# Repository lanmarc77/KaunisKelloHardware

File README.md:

# KaunisKelloHardware
Hardware schematics of the Kaunis Kello clock

[firmware is here](https://github.com/lanmarc77/KaunisKello)

[firmware compiler](https://myiq.de/cgi-bin/kk.pl)

[hardware schematics are here](https://github.com/lanmarc77/KaunisKelloHardware)

[MP3 module code is here](https://github.com/lanmarc77/KaunisKelloSoundModule)

[SD card sounds of the MP3 module are here](https://github.com/lanmarc77/KaunisKelloSounds)

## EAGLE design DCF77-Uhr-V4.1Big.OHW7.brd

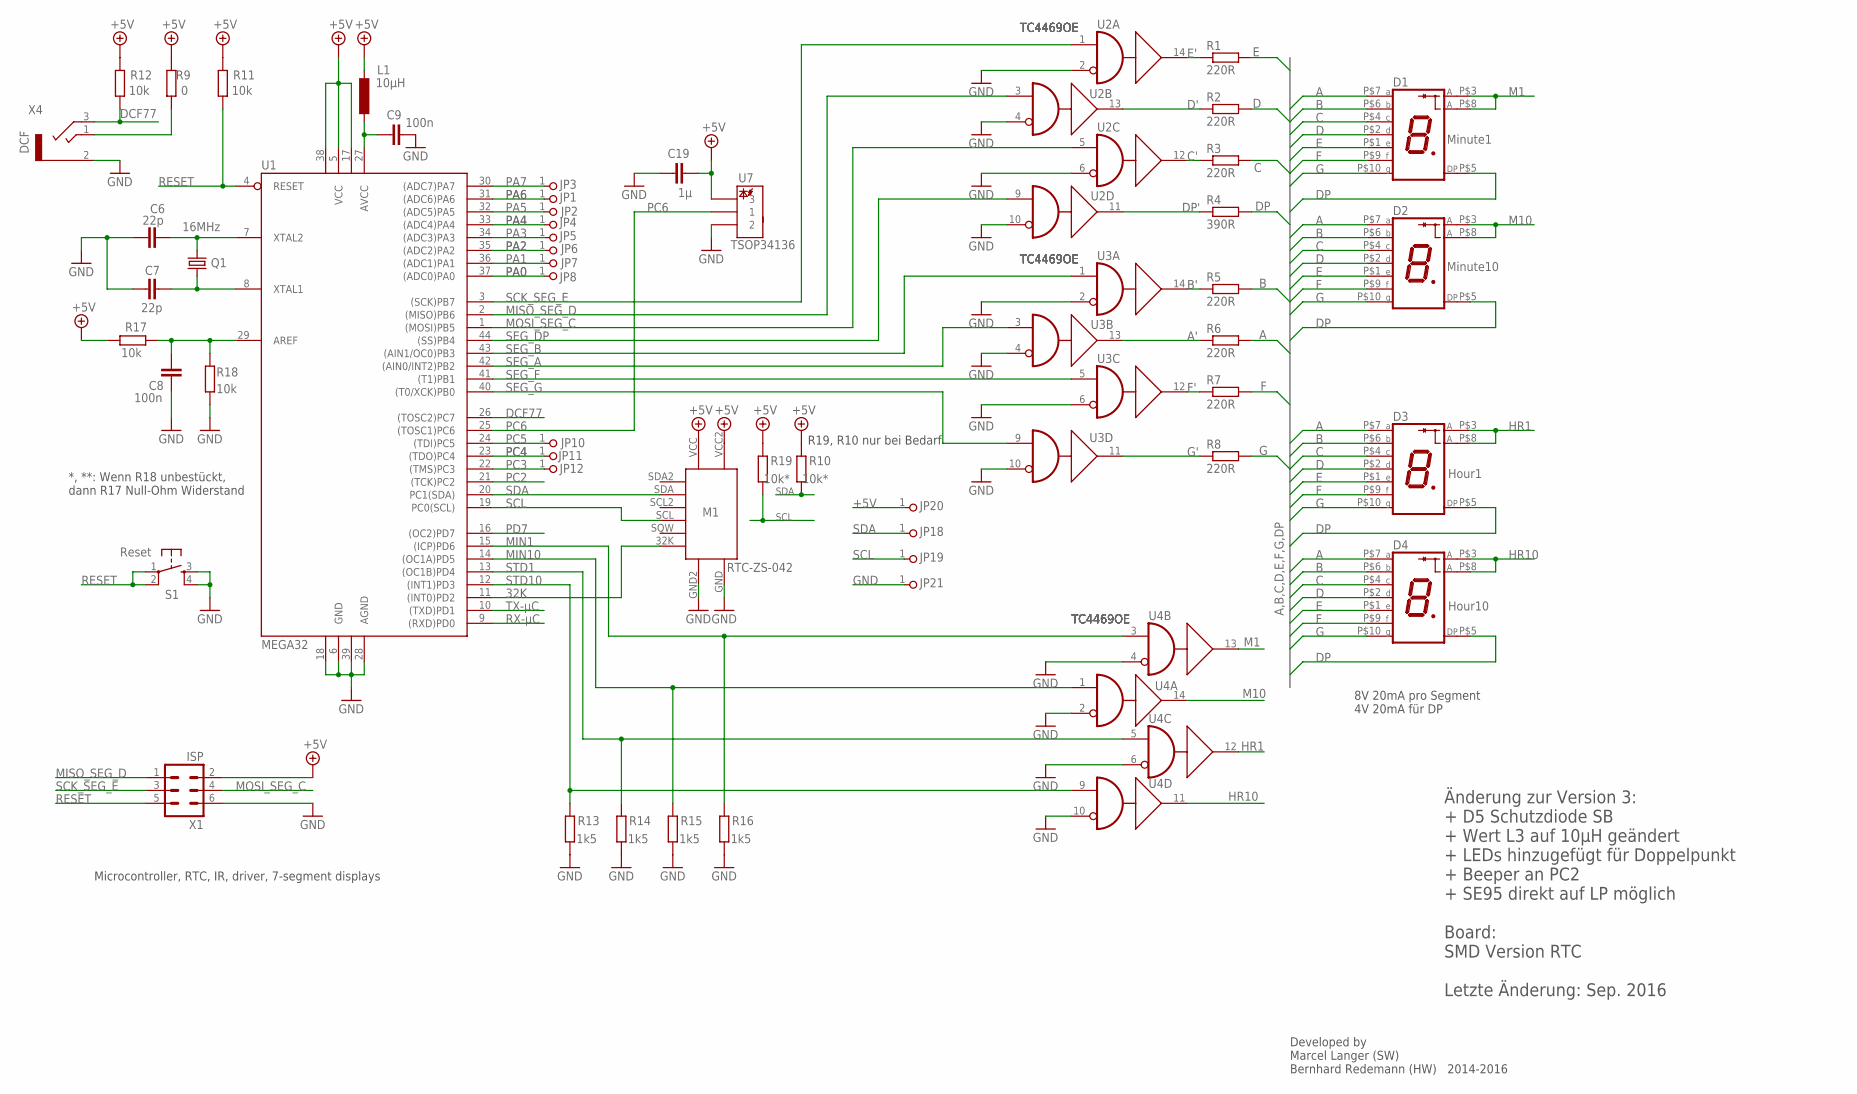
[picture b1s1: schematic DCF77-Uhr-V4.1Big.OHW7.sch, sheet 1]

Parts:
C6, C7: 22p; C0805
C8, C9: 100n; C0805
C19: 1µ; C0805
D1: Minute1; SA40-19EWA
D2: Minute10; SA40-19EWA
D3: Hour1; SA40-19EWA
D4: Hour10; SA40-19EWA
JP1, JP3: PA6; 1X01
JP2, JP10: PC5; 1X01
JP4: PA4; 1X01
JP5: PA3; 1X01
JP6: PA2; 1X01
JP7: PA1; 1X01
JP8: PA0; 1X01
JP11: PC4; 1X01
JP12: PC3; 1X01
JP18: SDA; 1X01
JP19: SCL; 1X01
JP20: +5V; 1X01
JP21: GND; 1X01
L1: 10µH; L2825P
M1: RTC-ZS-042; ZS-042-SMD
Q1: 16MHz; HC49UP
R1, R2, R3, R5, R6, R7, R8: 220R; M0805
R4: 390R; M0805
R9: 0; M0805
R10, R19: 10k*; M0805
R11, R12, R17, R18: 10k; M0805
R13, R14, R15, R16: 1k5; M0805
S1: Reset; DTSM-6
U1: MEGA32; TQFP44
U2, U3, U4: TC4469OE; SO-16DW
U7: TSOP34136; TSOP348
X1: ISP; ML6
X4: DCF; 1502_01

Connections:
32K: M1.32K, U1.11 ((INT0)PD2)
+5V: C19.2, JP20.1, L1.2, M1.VCC, M1.VCC2, R9.2, R10.2, R11.2, R12.2, R17.1, R19.2, U1.5 (VCC), U1.17 (VCC1), U1.38 (VCC2), U7.3, X1.2; also elsewhere on the board
A: D1.P$7 (A), D2.P$7 (A), D3.P$7 (A), D4.P$7 (A), R6.2
A': R6.1, U3.13 (Y)
AREF: C8.2, R17.2, R18.2, U1.29 (AREF)
B: D1.P$6 (B), D2.P$6 (B), D3.P$6 (B), D4.P$6 (B), R5.2
B': R5.1, U3.14 (Y)
C: D1.P$4 (C), D2.P$4 (C), D3.P$4 (C), D4.P$4 (C), R3.2
C': R3.1, U2.12 (Y)
D: D1.P$2 (D), D2.P$2 (D), D3.P$2 (D), D4.P$2 (D), R2.2
D': R2.1, U2.13 (Y)
DCF77: R12.1, U1.26 ((TOSC2)PC7), X4.3 (2)
DP: D1.P$5 (DP), D2.P$5 (DP), D3.P$5 (DP), D4.P$5 (DP), R4.2
DP': R4.1, U2.11 (Y)
E: D1.P$1 (E), D2.P$1 (E), D3.P$1 (E), D4.P$1 (E), R1.2
E': R1.1, U2.14 (Y)
F: D1.P$9 (F), D2.P$9 (F), D3.P$9 (F), D4.P$9 (F), R7.2
F': R7.1, U3.12 (Y)
G: D1.P$10 (G), D2.P$10 (G), D3.P$10 (G), D4.P$10 (G), R8.2
G': R8.1, U3.11 (Y)
GND: C6.1, C7.1, C8.1, C9.2, C19.1, JP21.1, M1.GND, M1.GND2, R13.1, R14.1, R15.1, R16.1, R18.1, S1.3, S1.4, U1.6 (GND), U1.18 (GND1), U1.28 (AGND), U1.39 (GND2), U2.2 (B), U2.4 (B), U2.6 (B), U2.10 (B), U3.2 (B), U3.4 (B), U3.6 (B), U3.10 (B), U4.2 (B), U4.4 (B), U4.6 (B), U4.10 (B), U7.2, X1.6, X4.2 (1); also elsewhere on the board
HR1: D3.P$3 (A), D3.P$8 (A), U4.12 (Y)
HR10: D4.P$3 (A), D4.P$8 (A), U4.11 (Y)
M1: D1.P$3 (A), D1.P$8 (A), U4.13 (Y)
M10: D2.P$3 (A), D2.P$8 (A), U4.14 (Y)
MIN1: R16.2, U1.15 ((ICP)PD6), U4.3 (A)
MIN10: R15.2, U1.14 ((OC1A)PD5), U4.1 (A)
MISO_SEG_D: U1.2 ((MISO)PB6), U2.3 (A), X1.1
MOSI_SEG_C: U1.1 ((MOSI)PB5), U2.5 (A), X1.4
unnamed: C6.2, Q1.2, U1.7 (XTAL2)
unnamed: C7.2, Q1.1, U1.8 (XTAL1)
unnamed: R9.1, X4.1 (3)
unnamed: C9.1, L1.1, U1.27 (AVCC)
PA0: JP8.1, U1.37 ((ADC0)PA0)
PA1: JP7.1, U1.36 ((ADC1)PA1)
PA2: JP6.1, U1.35 ((ADC2)PA2)
PA3: JP5.1, U1.34 ((ADC3)PA3)
PA4: JP4.1, U1.33 ((ADC4)PA4)
PA5: JP2.1, U1.32 ((ADC5)PA5)
PA6: JP1.1, U1.31 ((ADC6)PA6)
PA7: JP3.1, U1.30 ((ADC7)PA7)
PC2: U1.21 ((TCK)PC2); also elsewhere on the board
PC3: JP12.1, U1.22 ((TMS)PC3)
PC4: JP11.1, U1.23 ((TDO)PC4)
PC5: JP10.1, U1.24 ((TDI)PC5)
PC6: U1.25 ((TOSC1)PC6), U7.1
PD7: U1.16 ((OC2)PD7); also elsewhere on the board
RESET: R11.1, S1.1, S1.2, U1.4 (RESET), X1.5
RX-µC: U1.9 ((RXD)PD0); also elsewhere on the board
SCK_SEG_E: U1.3 ((SCK)PB7), U2.1 (A), X1.3
SCL: JP19.1, M1.SCL, R19.1, U1.19 (PC0(SCL)); also elsewhere on the board
SDA: JP18.1, M1.SDA, R10.1, U1.20 (PC1(SDA)); also elsewhere on the board
SEG_A: U1.42 ((AIN0/INT2)PB2), U3.3 (A)
SEG_B: U1.43 ((AIN1/OC0)PB3), U3.1 (A)
SEG_DP: U1.44 ((SS)PB4), U2.9 (A)
SEG_F: U1.41 ((T1)PB1), U3.5 (A)
SEG_G: U1.40 ((T0/XCK)PB0), U3.9 (A)
STD1: R14.2, U1.13 ((OC1B)PD4), U4.5 (A)
STD10: R13.2, U1.12 ((INT1)PD3), U4.9 (A)
TX-µC: U1.10 ((TXD)PD1); also elsewhere on the board

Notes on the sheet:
Microcontroller, RTC, IR, driver, 7-segment displays
Developed by Marcel Langer (SW) Bernhard Redemann (HW) 2014-2016
*, **: Wenn R18 unbestückt, dann R17 Null-Ohm Widerstand
8V 20mA pro Segment 4V 20mA für DP
R19, R10 nur bei Bedarf
Änderung zur Version 3: + D5 Schutzdiode SB + Wert L3 auf 10µH geändert + LEDs hinzugefügt für Doppelpunkt + Beeper an PC2 + SE95 direkt auf LP möglich Board: SMD Version RTC
Letzte Änderung: Sep. 2016

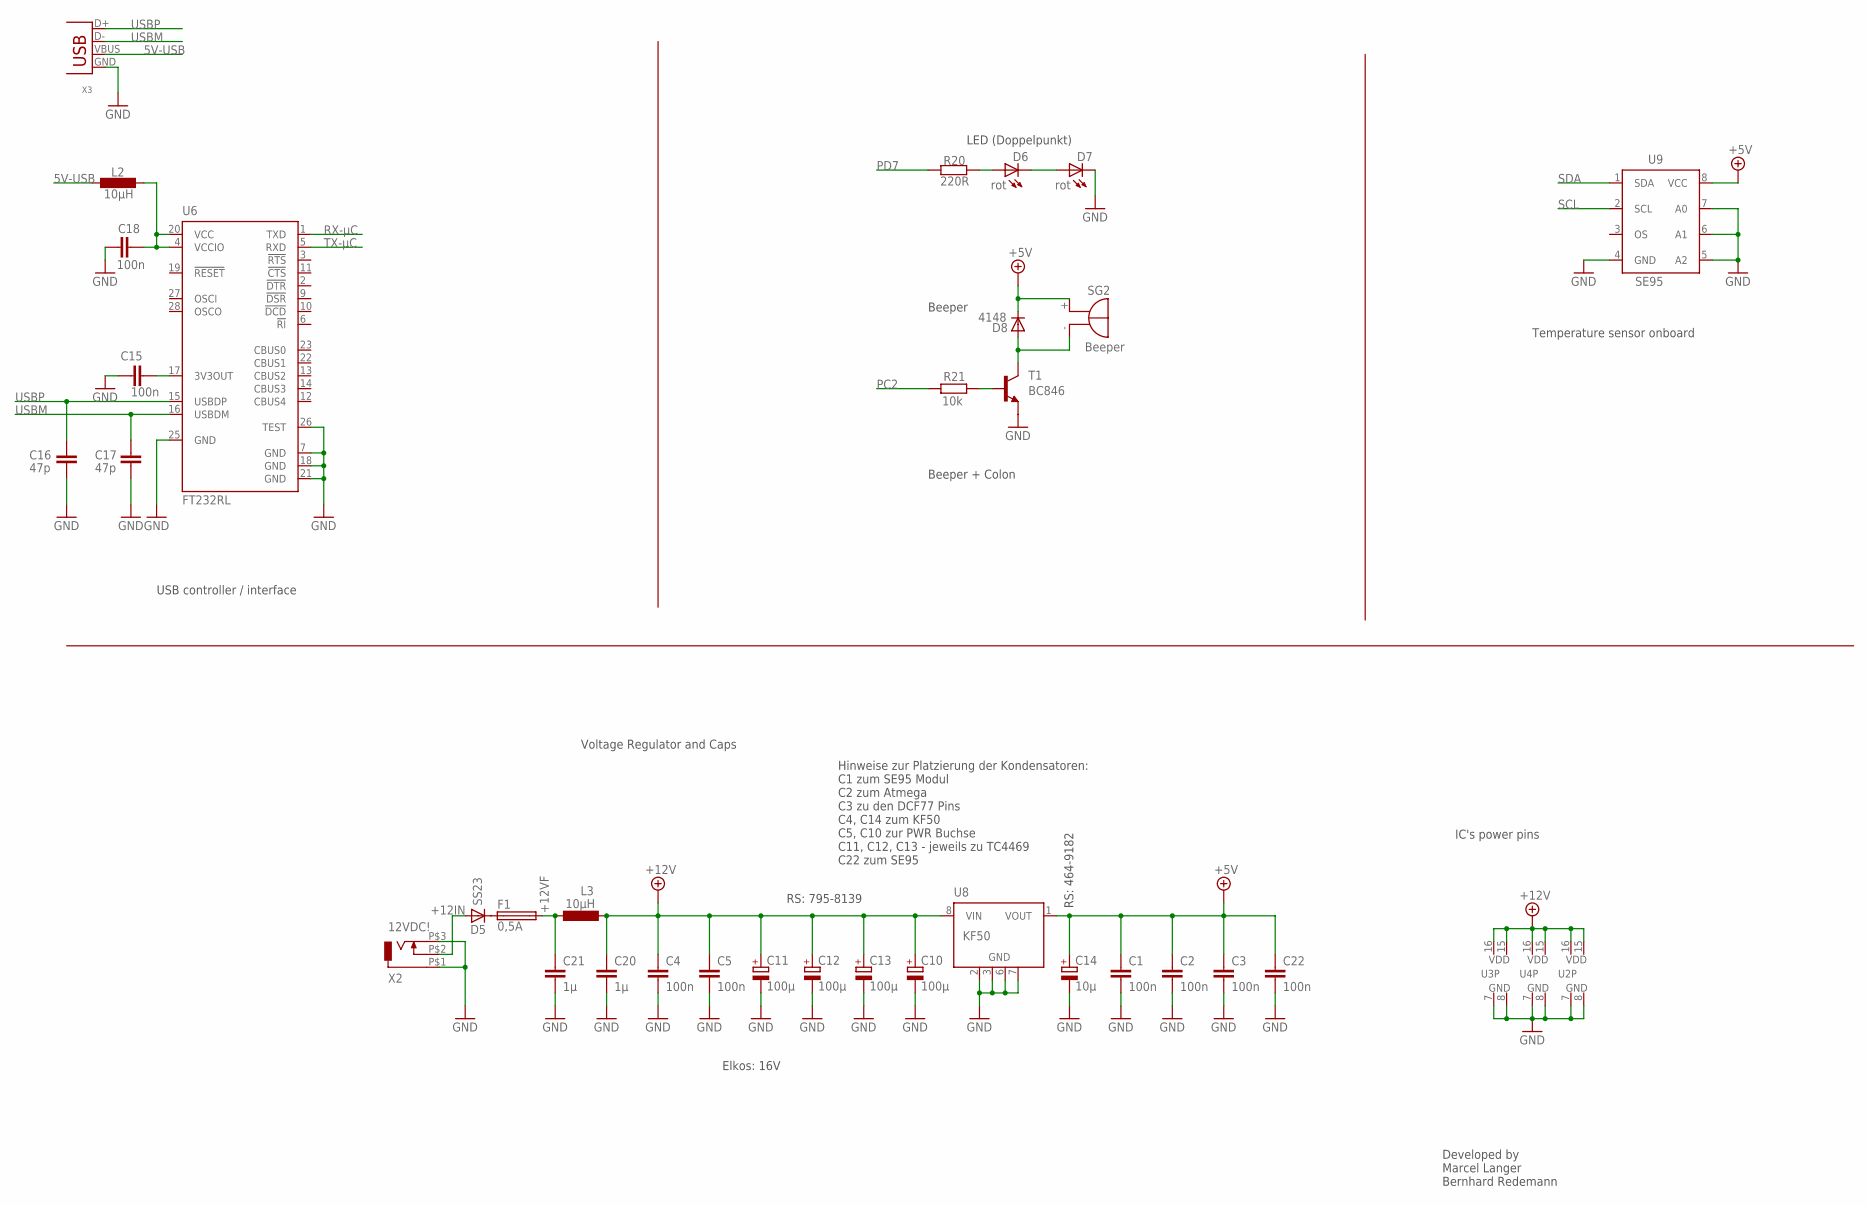
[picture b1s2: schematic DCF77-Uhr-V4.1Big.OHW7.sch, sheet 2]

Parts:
C1, C2, C3, C4, C5, C15, C18, C22: 100n; C0805
C10, C11, C12, C13: 100µ; PANASONIC_D
C14: 10µ; PANASONIC_B
C16, C17: 47p; C0805
C20, C21: 1µ; C0805
D5: SS23; SMB
D6, D7: rot; LED10MM
D8: 4148; DO214BA
F1: 0,5A; 19560
L2, L3: 10µH; L2825P
R20: 220R; M0805
R21: 10k; M0805
SG2: Beeper; BMT1205XH7.5
T1: BC846; SOT23
U2, U3, U4: TC4469OE; SO-16DW
U6: FT232RL; SSOP28
U8: KF50; SO08
U9: SE95; SO08
X2: 12VDC!; DCJ04-021
X3: USB; USB-B180

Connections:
5V-USB: L2.2, X3.VBUS
+5V: C1.1, C2.1, C3.1, C14.+, C22.1, D8.C, SG2.+, U8.1 (VOUT), U9.8 (VCC); also elsewhere on the board
+12IN: D5.A, X2.P$2 (2)
+12V: C4.1, C5.1, C10.+, C11.+, C12.+, C13.+, C20.1, L3.1, U2.15 (VDD), U2.16 (VDD), U3.15 (VDD), U3.16 (VDD), U4.15 (VDD), U4.16 (VDD), U8.8 (VIN)
+12VF: C21.1, F1.2, L3.2
GND: C1.2, C2.2, C3.2, C4.2, C5.2, C10.-, C11.-, C12.-, C13.-, C14.-, C15.1, C16.1, C17.1, C18.1, C20.2, C21.2, C22.2, D7.K (C), T1.2 (E), U2.7 (GND), U2.8 (GND), U3.7 (GND), U3.8 (GND), U4.7 (GND), U4.8 (GND), U6.7 (GND), U6.18 (GND), U6.21 (GND), U6.25 (GND), U6.26 (TEST), U8.2 (GND), U8.3 (GND), U8.6 (GND), U8.7 (GND), U9.4 (GND), U9.5 (A2), U9.6 (A1), U9.7 (A0), X2.P$1 (1), X2.P$3 (3), X3.GND; also elsewhere on the board
unnamed: D5.C, F1.1
unnamed: D6.A, R20.2
unnamed: D6.K (C), D7.A
unnamed: R21.1, T1.1 (B)
unnamed: D8.A, SG2.-, T1.3 (C)
unnamed: C15.2, U6.17 (3V3OUT)
unnamed: C18.2, L2.1, U6.4 (VCCIO), U6.20 (VCC)
PC2: R21.2; also elsewhere on the board
PD7: R20.1; also elsewhere on the board
RX-µC: U6.1 (TXD); also elsewhere on the board
SCL: U9.2 (SCL); also elsewhere on the board
SDA: U9.1 (SDA); also elsewhere on the board
TX-µC: U6.5 (RXD); also elsewhere on the board
USBM: C17.2, U6.16 (USBDM), X3.D-
USBP: C16.2, U6.15 (USBDP), X3.D+

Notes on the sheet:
USB controller / interface
Voltage Regulator and Caps
Hinweise zur Platzierung der Kondensatoren: C1 zum SE95 Modul C2 zum Atmega C3 zu den DCF77 Pins C4, C14 zum KF50 C5, C10 zur PWR Buchse C11, C12, C13 - jeweils zu TC4469 C22 zum SE95
Elkos: 16V
RS: 464-9182
RS: 795-8139
LED (Doppelpunkt)
Beeper
Temperature sensor onboard
Beeper + Colon
Developed by Marcel Langer Bernhard Redemann
IC's power pins

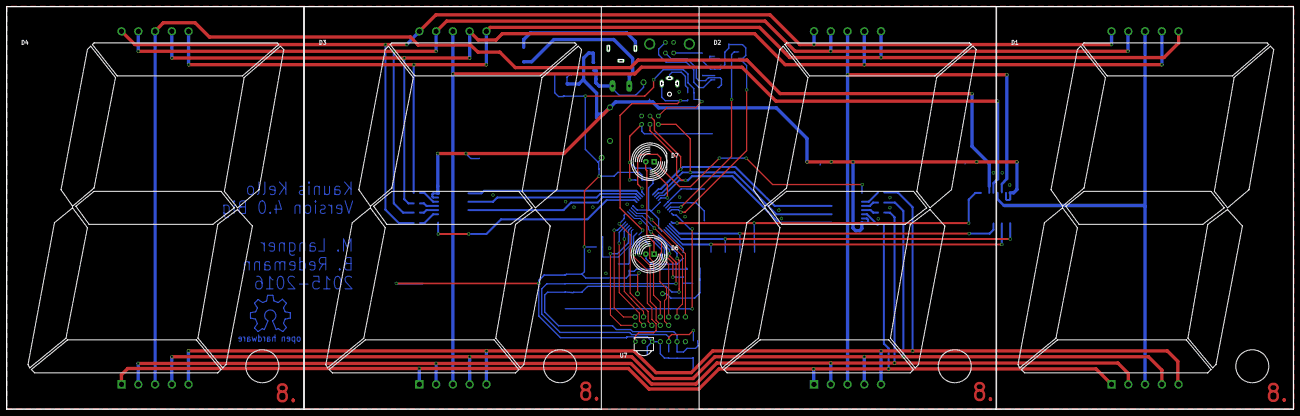
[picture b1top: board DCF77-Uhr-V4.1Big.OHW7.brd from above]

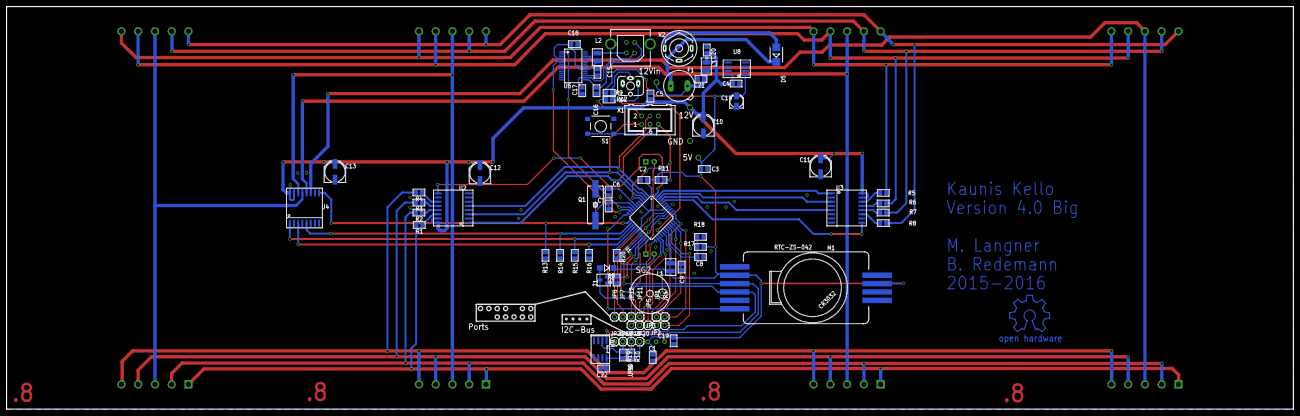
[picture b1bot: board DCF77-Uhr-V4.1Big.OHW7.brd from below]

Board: 2 copper layers, 390.0 x 122.0 mm, 88 parts (81 on the bottom side), 73 nets.

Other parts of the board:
U$1: OPEN_HARDWARE
